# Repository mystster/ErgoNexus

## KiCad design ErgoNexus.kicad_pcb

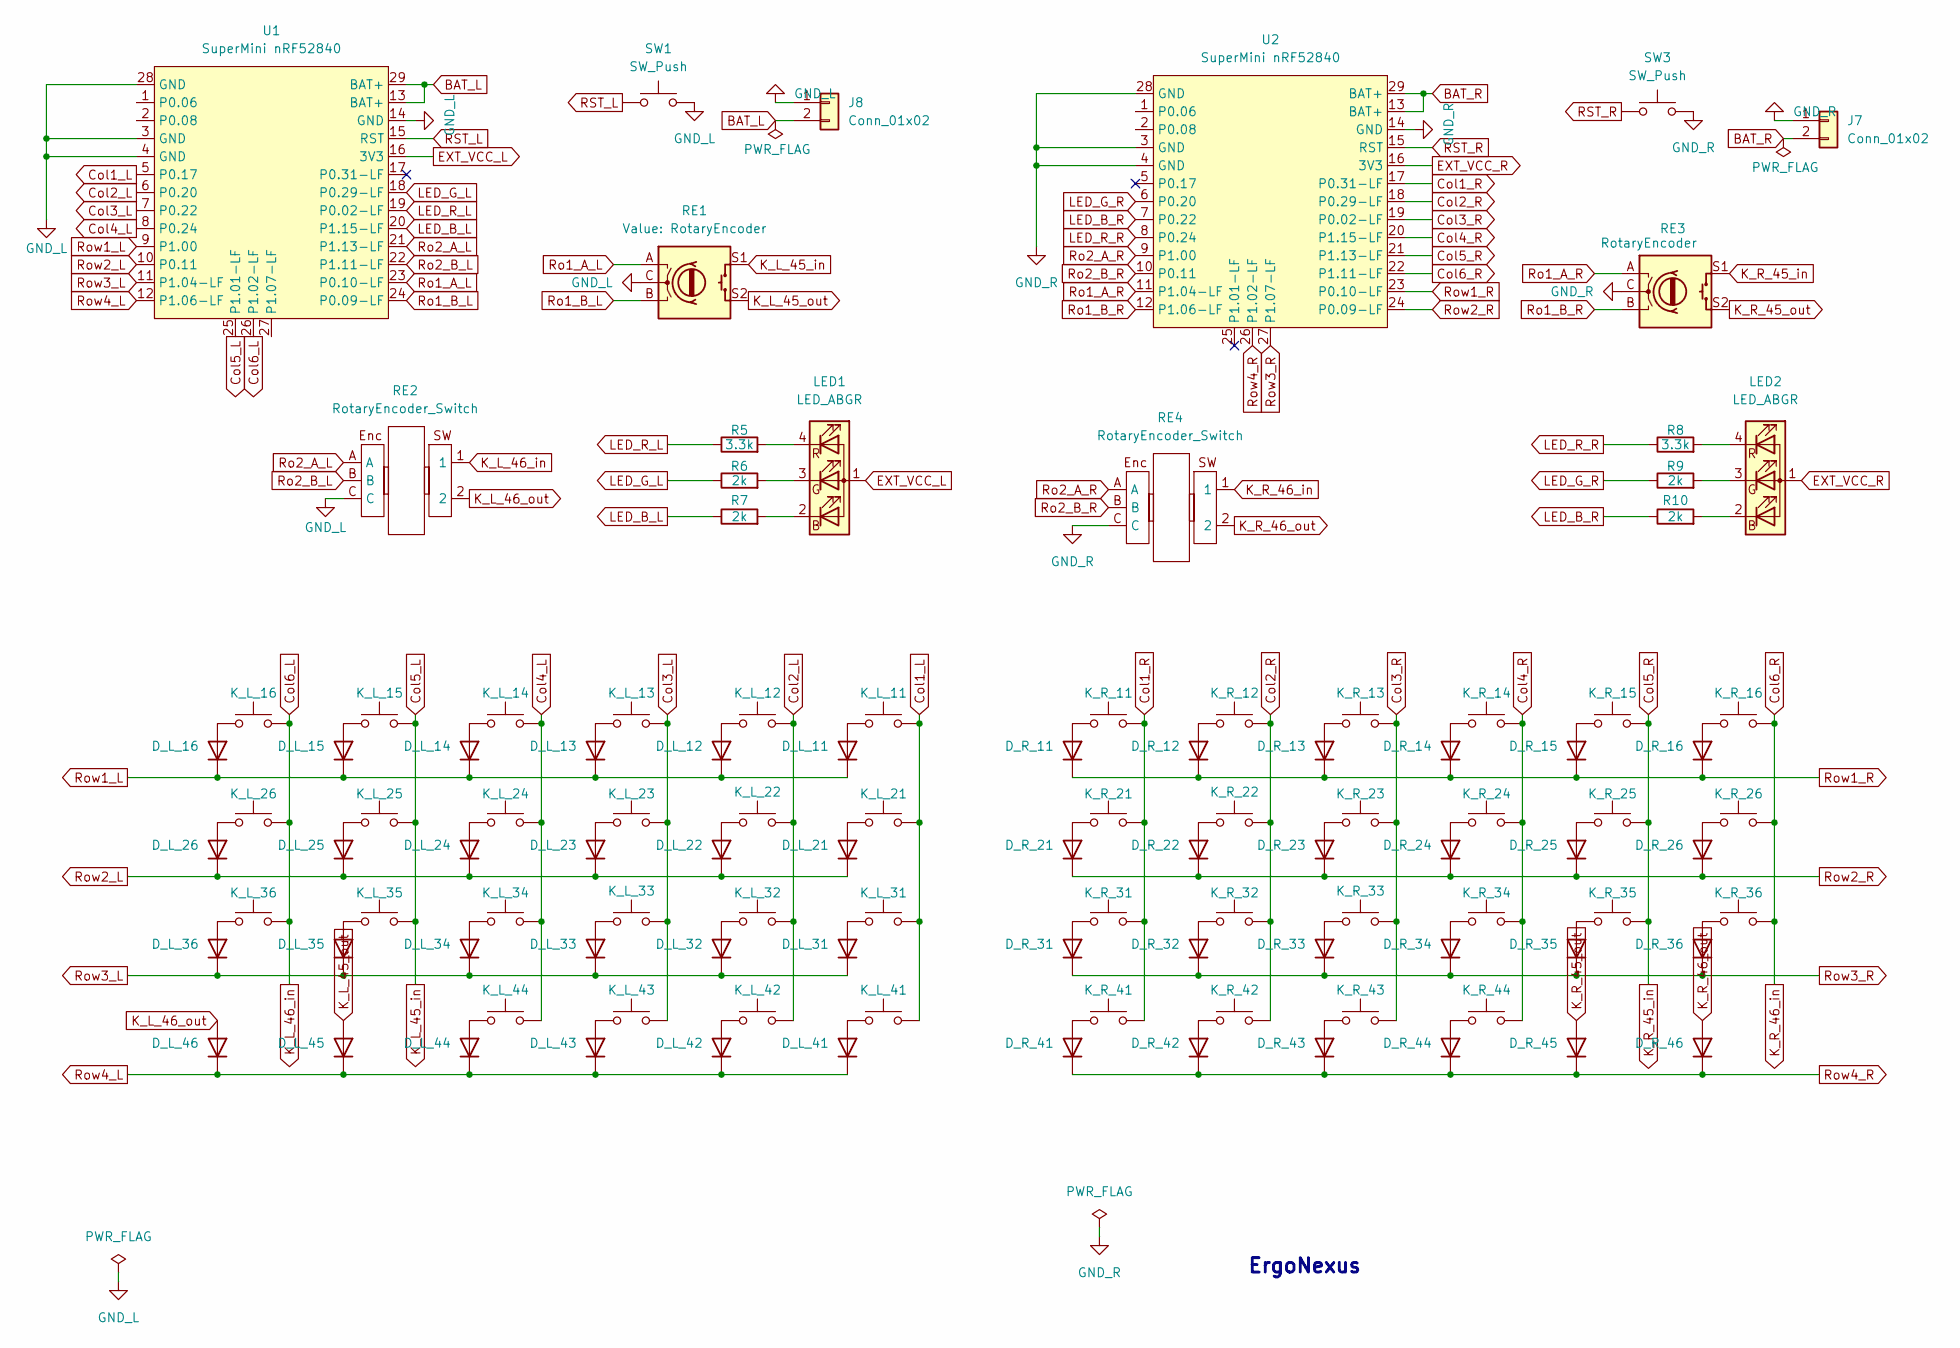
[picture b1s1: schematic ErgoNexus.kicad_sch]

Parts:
D_L_11, D_L_12, D_L_13, D_L_14, D_L_15, D_L_16, D_L_21, D_L_22, D_L_23, D_L_24, D_L_25, D_L_26, D_L_31, D_L_32, D_L_33, D_L_34, D_L_35, D_L_36, D_L_41, D_L_42, D_L_43, D_L_44, D_L_45, D_L_46: 1N4148SW; D_SOD-323; LCSC C2128
D_R_11, D_R_12, D_R_13, D_R_14, D_R_15, D_R_16, D_R_21, D_R_22, D_R_23, D_R_24, D_R_25, D_R_26, D_R_31, D_R_32, D_R_33, D_R_34, D_R_35, D_R_36, D_R_41, D_R_42, D_R_43, D_R_44, D_R_45, D_R_46: 1N4148SW; D_SOD-323; LCSC C2128
J7, J8: Conn_01x02; JST_PH_S2B-PH-K_1x02_P2.00mm_Horizontal
K_L_11, K_L_12, K_L_13, K_L_14, K_L_15, K_L_16, K_L_21, K_L_22, K_L_23, K_L_24, K_L_25, K_L_26, K_L_31, K_L_32, K_L_33, K_L_34, K_L_35, K_L_36, K_L_41, K_L_42, K_L_43, K_L_44: SW_Push; GatronLP_Hotswap_1u
K_R_11, K_R_12, K_R_13, K_R_14, K_R_15, K_R_16, K_R_21, K_R_22, K_R_23, K_R_24, K_R_25, K_R_26, K_R_31, K_R_32, K_R_33, K_R_34, K_R_35, K_R_36, K_R_41, K_R_42, K_R_43, K_R_44: SW_Push; GatronLP_Hotswap_1u
LED1, LED2: LED_ABGR; LED Rectangle(OSTBMAZ2C1D)
R5, R8: 3.3k; R_0402; LCSC C25890
R6, R7, R9, R10: 2k; R_0402; LCSC C4109
RE1, RE3: RotaryEncoder; RotaryEncoder_EC11
RE2, RE4: RotaryEncoder_Switch; THQWGD001C [2pin] #2
SW1, SW3: SW_Push; ResetSW
U1, U2: SuperMini nRF52840; SuperMini_nRF52840_AH_USBup

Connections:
BAT_L: J8.2, U1.13 (BAT+), U1.29 (BAT+)
BAT_R: J7.2, U2.13 (BAT+), U2.29 (BAT+)
Col1_L: K_L_11.1, K_L_21.1, K_L_31.1, K_L_41.1, U1.5 (P0.17)
Col1_R: K_R_11.1, K_R_21.1, K_R_31.1, K_R_41.1, U2.17 (P0.31-LF)
Col2_L: K_L_12.1, K_L_22.1, K_L_32.1, K_L_42.1, U1.6 (P0.20)
Col2_R: K_R_12.1, K_R_22.1, K_R_32.1, K_R_42.1, U2.18 (P0.29-LF)
Col3_L: K_L_13.1, K_L_23.1, K_L_33.1, K_L_43.1, U1.7 (P0.22)
Col3_R: K_R_13.1, K_R_23.1, K_R_33.1, K_R_43.1, U2.19 (P0.02-LF)
Col4_L: K_L_14.1, K_L_24.1, K_L_34.1, K_L_44.1, U1.8 (P0.24)
Col4_R: K_R_14.1, K_R_24.1, K_R_34.1, K_R_44.1, U2.20 (P1.15-LF)
Col5_L: K_L_15.1, K_L_25.1, K_L_35.1, RE1.S1, U1.25 (P1.01-LF)
Col5_R: K_R_15.1, K_R_25.1, K_R_35.1, RE3.S1, U2.21 (P1.13-LF)
Col6_L: K_L_16.1, K_L_26.1, K_L_36.1, RE2.1, U1.26 (P1.02-LF)
Col6_R: K_R_16.1, K_R_26.1, K_R_36.1, RE4.1, U2.22 (P1.11-LF)
EXT_VCC_L: LED1.1 (A), U1.16 (3V3)
EXT_VCC_R: LED2.1 (A), U2.16 (3V3)
GND_L: J8.1, RE1.C, RE2.C, SW1.2, U1.3 (GND), U1.4 (GND), U1.14 (GND), U1.28 (GND)
GND_R: J7.1, RE3.C, RE4.C, SW3.2, U2.3 (GND), U2.4 (GND), U2.14 (GND), U2.28 (GND)
K_L_45_out: D_L_45.2 (A), RE1.S2
K_L_46_out: D_L_46.2 (A), RE2.2
K_R_45_out: D_R_45.2 (A), RE3.S2
K_R_46_out: D_R_46.2 (A), RE4.2
LED_B_L: R7.1, U1.20 (P1.15-LF)
LED_B_R: R10.1, U2.7 (P0.22)
LED_G_L: R6.1, U1.18 (P0.29-LF)
LED_G_R: R9.1, U2.6 (P0.20)
LED_R_L: R5.1, U1.19 (P0.02-LF)
LED_R_R: R8.1, U2.8 (P0.24)
unnamed: D_L_11.2 (A), K_L_11.2
unnamed: D_L_12.2 (A), K_L_12.2
unnamed: D_L_13.2 (A), K_L_13.2
unnamed: D_L_14.2 (A), K_L_14.2
unnamed: D_L_15.2 (A), K_L_15.2
unnamed: D_L_16.2 (A), K_L_16.2
unnamed: D_L_21.2 (A), K_L_21.2
unnamed: D_L_22.2 (A), K_L_22.2
unnamed: D_L_23.2 (A), K_L_23.2
unnamed: D_L_24.2 (A), K_L_24.2
unnamed: D_L_25.2 (A), K_L_25.2
unnamed: D_L_26.2 (A), K_L_26.2
unnamed: D_L_31.2 (A), K_L_31.2
unnamed: D_L_32.2 (A), K_L_32.2
unnamed: D_L_33.2 (A), K_L_33.2
unnamed: D_L_34.2 (A), K_L_34.2
unnamed: D_L_35.2 (A), K_L_35.2
unnamed: D_L_36.2 (A), K_L_36.2
unnamed: D_L_41.2 (A), K_L_41.2
unnamed: D_L_42.2 (A), K_L_42.2
unnamed: D_L_43.2 (A), K_L_43.2
unnamed: D_L_44.2 (A), K_L_44.2
unnamed: D_R_11.2 (A), K_R_11.2
unnamed: D_R_12.2 (A), K_R_12.2
unnamed: D_R_13.2 (A), K_R_13.2
unnamed: D_R_14.2 (A), K_R_14.2
unnamed: D_R_15.2 (A), K_R_15.2
unnamed: D_R_16.2 (A), K_R_16.2
unnamed: D_R_21.2 (A), K_R_21.2
unnamed: D_R_22.2 (A), K_R_22.2
unnamed: D_R_23.2 (A), K_R_23.2
unnamed: D_R_24.2 (A), K_R_24.2
unnamed: D_R_25.2 (A), K_R_25.2
unnamed: D_R_26.2 (A), K_R_26.2
unnamed: D_R_31.2 (A), K_R_31.2
unnamed: D_R_32.2 (A), K_R_32.2
unnamed: D_R_33.2 (A), K_R_33.2
unnamed: D_R_34.2 (A), K_R_34.2
unnamed: D_R_35.2 (A), K_R_35.2
unnamed: D_R_36.2 (A), K_R_36.2
unnamed: D_R_41.2 (A), K_R_41.2
unnamed: D_R_42.2 (A), K_R_42.2
unnamed: D_R_43.2 (A), K_R_43.2
unnamed: D_R_44.2 (A), K_R_44.2
unnamed: LED1.2 (BK), R7.2
unnamed: LED1.3 (GK), R6.2
unnamed: LED1.4 (RK), R5.2
unnamed: LED2.2 (BK), R10.2
unnamed: LED2.3 (GK), R9.2
unnamed: LED2.4 (RK), R8.2
RST_L: SW1.1, U1.15 (RST)
RST_R: SW3.1, U2.15 (RST)
Ro1_A_L: RE1.A, U1.23 (P0.10-LF)
Ro1_A_R: RE3.A, U2.11 (P1.04-LF)
Ro1_B_L: RE1.B, U1.24 (P0.09-LF)
Ro1_B_R: RE3.B, U2.12 (P1.06-LF)
Ro2_A_L: RE2.A, U1.21 (P1.13-LF)
Ro2_A_R: RE4.A, U2.9 (P1.00)
Ro2_B_L: RE2.B, U1.22 (P1.11-LF)
Ro2_B_R: RE4.B, U2.10 (P0.11)
Row1_L: D_L_11.1 (K), D_L_12.1 (K), D_L_13.1 (K), D_L_14.1 (K), D_L_15.1 (K), D_L_16.1 (K), U1.9 (P1.00)
Row1_R: D_R_11.1 (K), D_R_12.1 (K), D_R_13.1 (K), D_R_14.1 (K), D_R_15.1 (K), D_R_16.1 (K), U2.23 (P0.10-LF)
Row2_L: D_L_21.1 (K), D_L_22.1 (K), D_L_23.1 (K), D_L_24.1 (K), D_L_25.1 (K), D_L_26.1 (K), U1.10 (P0.11)
Row2_R: D_R_21.1 (K), D_R_22.1 (K), D_R_23.1 (K), D_R_24.1 (K), D_R_25.1 (K), D_R_26.1 (K), U2.24 (P0.09-LF)
Row3_L: D_L_31.1 (K), D_L_32.1 (K), D_L_33.1 (K), D_L_34.1 (K), D_L_35.1 (K), D_L_36.1 (K), U1.11 (P1.04-LF)
Row3_R: D_R_31.1 (K), D_R_32.1 (K), D_R_33.1 (K), D_R_34.1 (K), D_R_35.1 (K), D_R_36.1 (K), U2.27 (P1.07-LF)
Row4_L: D_L_41.1 (K), D_L_42.1 (K), D_L_43.1 (K), D_L_44.1 (K), D_L_45.1 (K), D_L_46.1 (K), U1.12 (P1.06-LF)
Row4_R: D_R_41.1 (K), D_R_42.1 (K), D_R_43.1 (K), D_R_44.1 (K), D_R_45.1 (K), D_R_46.1 (K), U2.26 (P1.02-LF)

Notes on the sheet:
ErgoNexus

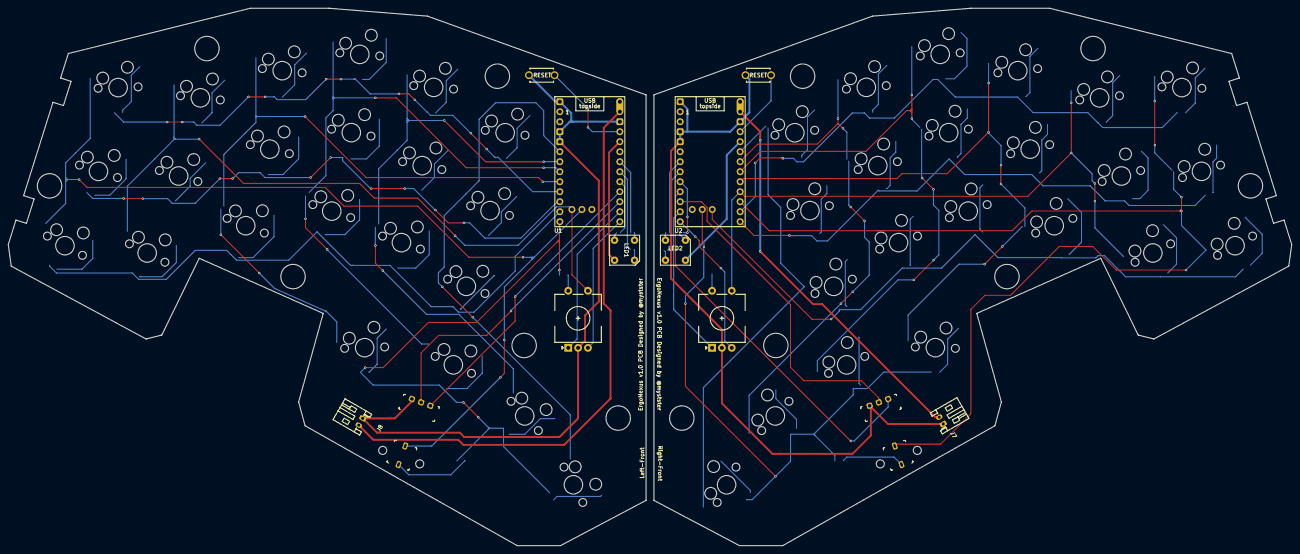
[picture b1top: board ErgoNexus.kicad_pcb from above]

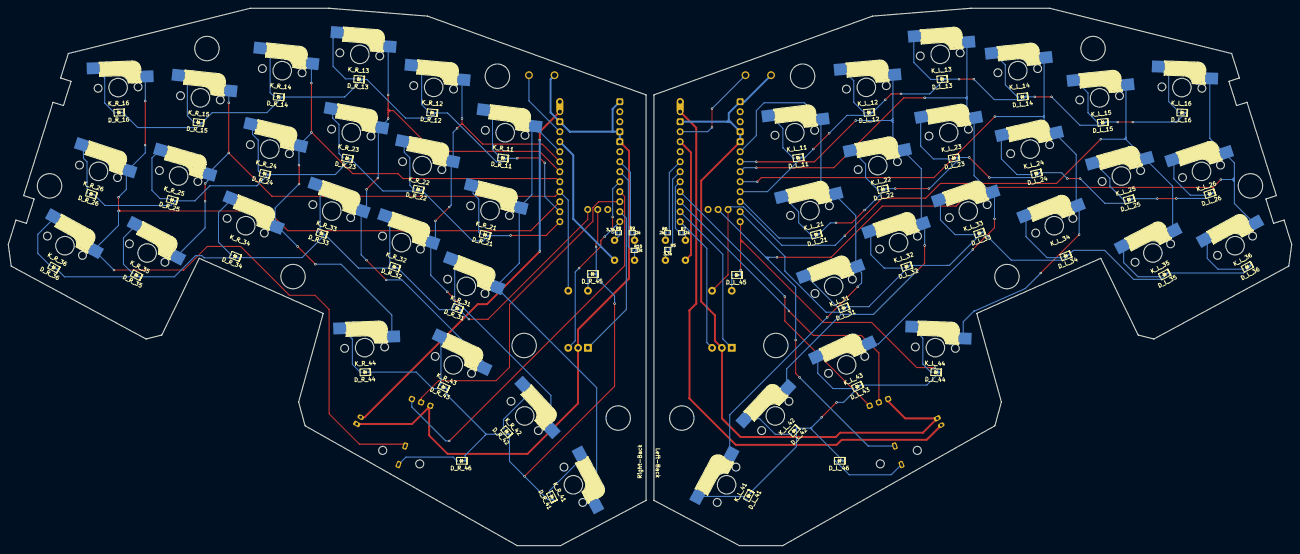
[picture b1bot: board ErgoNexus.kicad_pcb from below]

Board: 2 copper layers, 326.0 x 136.5 mm, 110 parts (56 on the bottom side), 96 nets.

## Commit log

2025-06-06 回路図が完成
2025-06-06 不要なファイルを削除
2025-06-13 pinアサインの変更 Fixes #1
2025-06-13 chore: add .gitignore file
    .gitignoreにバックアップファイルと一時ファイルを追加して、リポジトリ内に不要なファイルが含まれないようにしました。
2025-06-14 chore(gitignore): update ignore patterns
    バックアップファイルと一時ファイルのパターンを追加しました。
2025-06-14 fix: forget spi cs pin
2025-11-10 feat: 右手のレイアウトを設定
2025-11-10 chore: remove Cuts
2025-11-14 fix: 右手の配線を完成
2025-11-14 feat: 回路図においてキースイッチをマトリックス配列に変更
2025-11-14 feat: PCBにおいてアノテーションを対応付け
2025-11-15 fix: not fully annotation
2025-11-15 feat: finish wire for right
2025-11-16 feat: add screw hole
2025-11-16 fix: fix oled angle
2025-11-16 fix: 外形の変更
2025-11-16 fix: change battery connector rotation
2025-11-16 chore: add few 3d models
2025-11-16 fix: change oled rotation
2025-11-16 fix: battery connector position
2025-11-16 feat: add copy right to front silk
2025-12-14 feat: 左手の回路図の配置を修正
2025-12-19 feat: 左手の配線完了
2025-12-19 chore: jlcpcb向けのデータを出力
2025-12-24 fix: 左右のキーボードを合わせることで、jlcpcb向けデータが正しく出力されるように
2025-12-24 feat: フィレットとVカットの追加
2025-12-24 fix: ネジ穴を調整
2026-03-14 feat: remove one key and oled. little finger place update
2026-04-12 feat: 右側の配線完了
2026-04-17 feat: ケース用の回路図などを追加
2026-04-26 feat: 基板形状の変更
2026-04-29 feat: 左側の配線が完了
2026-04-29 fix: キーソケットをGatronLP(KS-33B)用に変更
2026-05-03 feat: add mouse bites
2026-05-04 feat: add tooling holes and fiducials
2026-05-05 feat: 水平ロータリーエンコーダのスイッチ部品を変更
    元々の11mmだと高すぎるのでエンコーダを7mmに変更。
    それに伴い、switchも高さの低いものに変更する必要があり、フットプリントを変更
2026-05-06 chore: remove unused files
2026-05-06 feat: change rotary encoder position
2026-05-06 chore: update gitignore
2026-05-11 feat: 水平ロータリーエンコーダの向きを変更
2026-05-11 feat: 親指キーを少し上に変更
2026-05-14 fix: ルールチェックエラーの修正
2026-05-16 refactor: clean up
2026-05-16 feat: remove mousebites and frame
2026-05-16 feat: add mousebite and frame using kikit
2026-05-17 feat: add assembly info and fix diode footprint
2026-05-17 feat: add serial text
2026-05-17 fix: 線の位置を調整
2026-05-20 fix: remove tooling holes
2026-05-21 feat: 端に磁石用の切り込みを追加
2026-05-30 feat: add gerber files.
2026-05-30 refactor: remove unused files
2026-05-30 fix: バッテリーコネクタの配線が逆になっていたのを修正
2026-05-30 feat: バッテリーコネクタを表面へ移動
    裏面だとコネクタが高すぎて、キーボード全体の高さが高くなってしまうため。
